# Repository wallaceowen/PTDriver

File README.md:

# PTDriver
Signal conditioning PT100 sensors for use with standard thermistor inputs on 3D printer control boards

## The schematic

## The board (KiCAD rendering)

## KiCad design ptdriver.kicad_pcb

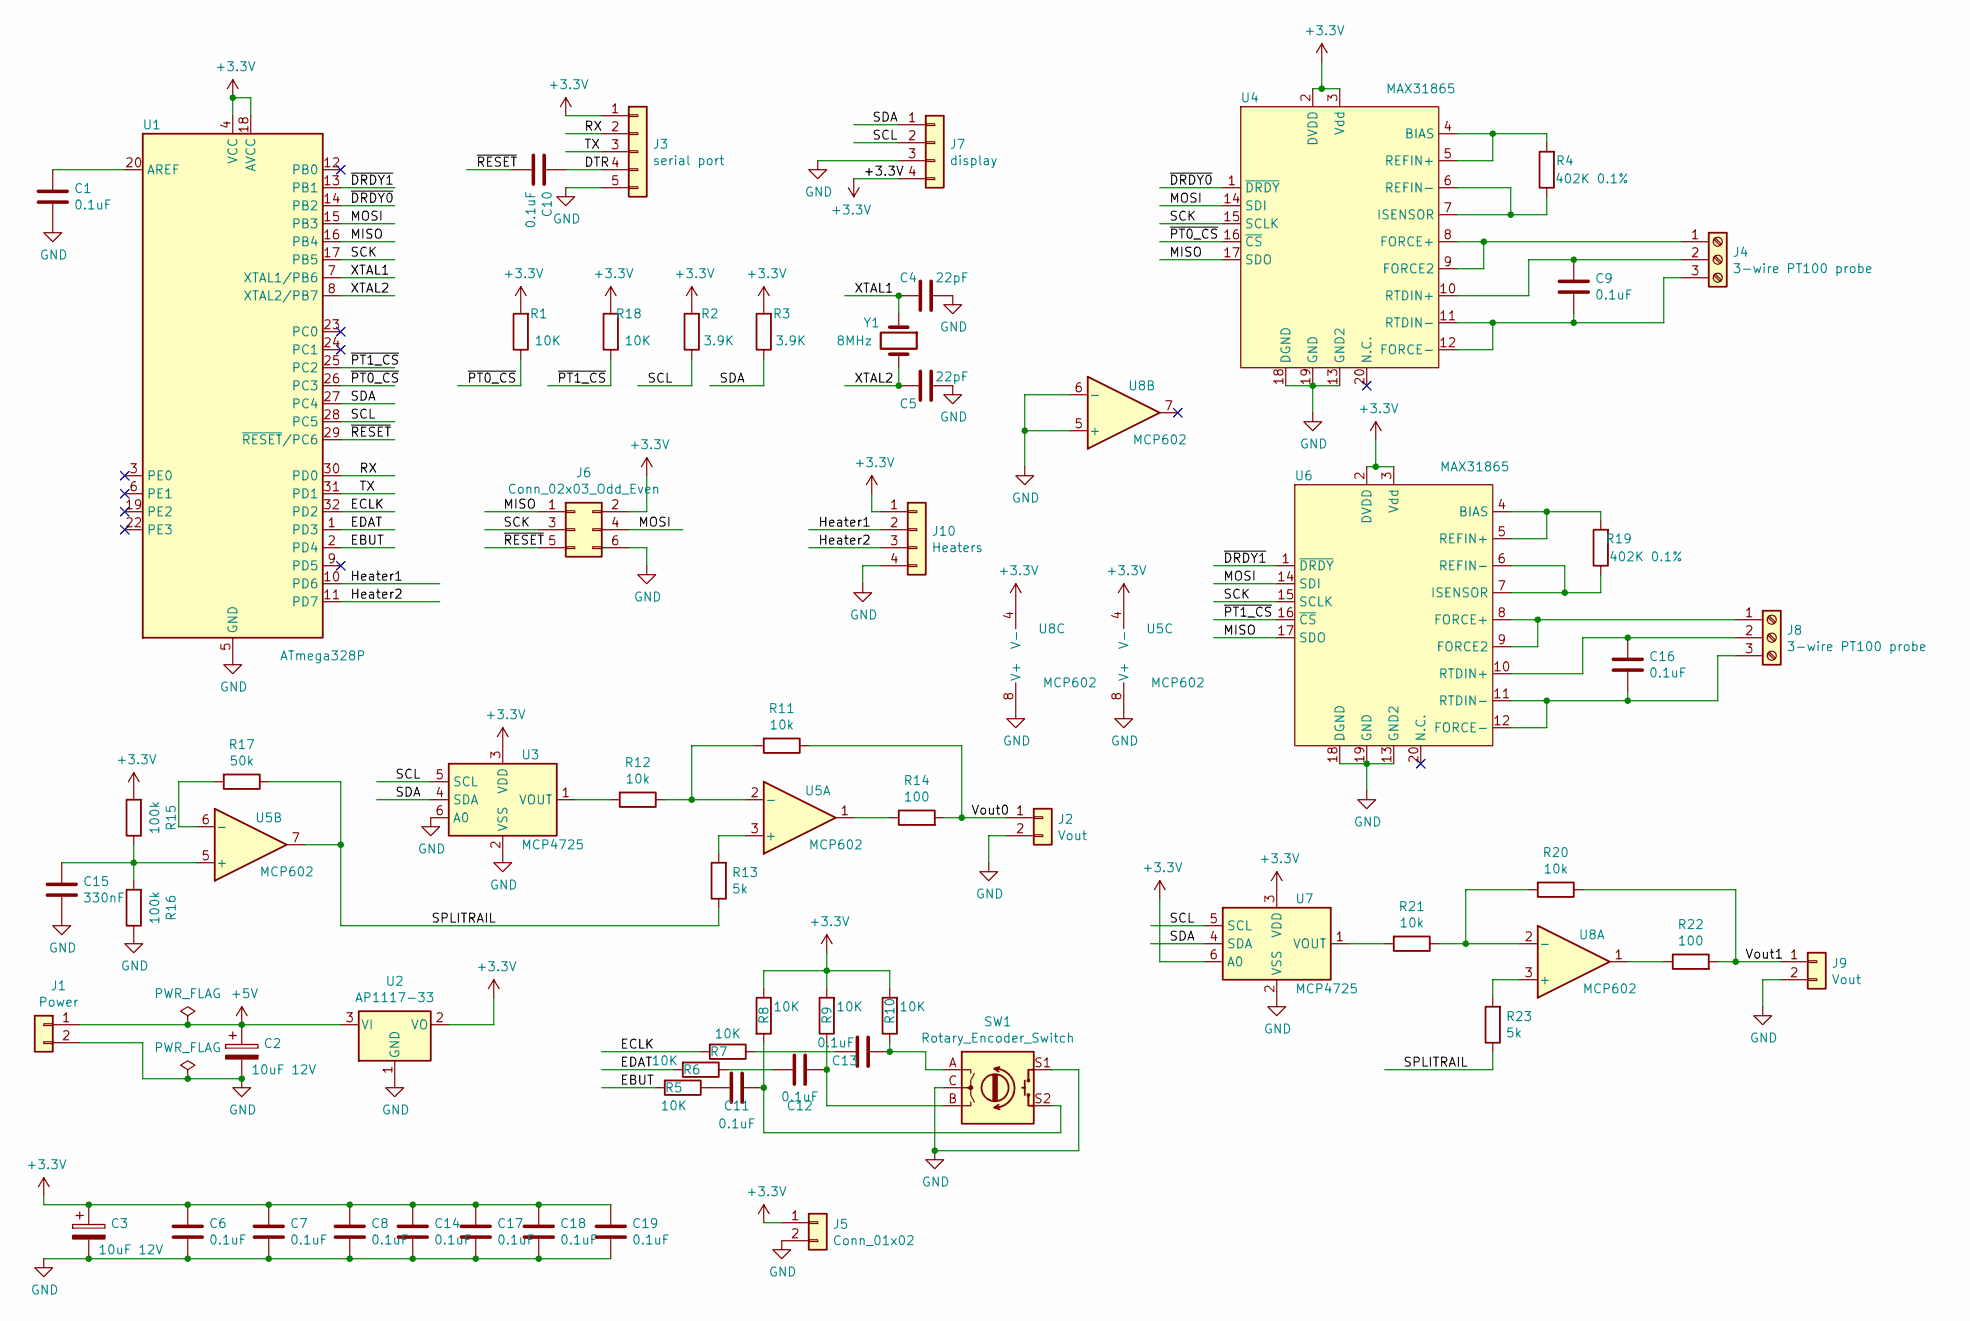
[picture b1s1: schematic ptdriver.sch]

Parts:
C1, C6, C7, C8, C9, C10, C14, C16, C17, C18, C19: 0.1uF; C_0805_2012Metric
C2, C3: 10uF 12V; C_2220_5650Metric
C4, C5: 22pF; C_0805_2012Metric
C11, C12, C13: 0.1uF; C_0603_1608Metric
C15: 330nF; C_0805_2012Metric
J1: Power; PinHeader_1x02_P2.54mm_Vertical
J2, J9: Vout; PinHeader_1x02_P2.54mm_Vertical
J3: serial port; PinHeader_1x05_P2.54mm_Vertical
J4, J8: 3-wire PT100 probe; TerminalBlock_4Ucon_1x03_P3.50mm_Vertical
J5: Conn_01x02; PinHeader_1x02_P2.54mm_Vertical
J6: Conn_02x03_Odd_Even; PinHeader_2x03_P2.54mm_Vertical
J7: display; PinHeader_1x04_P2.54mm_Vertical
J10: Heaters; PinHeader_1x04_P2.54mm_Vertical
R1, R5, R6, R7, R8, R9, R10, R18: 10K; R_0603_1608Metric
R2, R3: 3.9K; R_0603_1608Metric
R4, R19: 402K 0.1%; R_0805_2012Metric
R11, R12, R20, R21: 10k; R_0603_1608Metric
R13, R23: 5k; R_0603_1608Metric
R14, R22: 100; R_0603_1608Metric
R15, R16: 100k; R_0603_1608Metric
R17: 50k; R_0603_1608Metric
SW1: Rotary_Encoder_Switch; RotaryEncoder_Alps_EC12E-Switch_Vertical_H20mm_CircularMoun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
U1: ATmega328P; TQFP-32_7x7mm_P0.8mm
U2: AP1117-33; SOT-223-3_TabPin2
U3, U7: MCP4725; SOT-23-6_Handsoldering
U4, U6: MAX31865; SOP20_max
U5, U8: MCP602; SOIC-8_3.9x4.9mm_P1.27mm
Y1: 8MHz; Crystal_HC18-U_Vertical

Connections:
+3V3: C3.1, C6.1, C7.1, C8.1, C14.1, C17.1, C18.1, C19.1, J3.1, J5.1, J6.2, J7.4, J10.1, R1.2, R2.2, R3.2, R8.1, R9.2, R10.2, R15.2, R18.2, U1.4 (VCC), U1.18 (AVCC), U2.2 (VO), U3.3 (VDD), U4.2 (DVDD), U4.3 (Vdd), U5.4 (V-), U6.2 (DVDD), U6.3 (Vdd), U7.3 (VDD), U7.6 (A0), U8.4 (V-)
+5V: C2.1, J1.1, U2.3 (VI)
/DTR: C10.1, J3.4
/EBUT: R5.2, U1.2 (PD4)
/ECLK: R7.2, U1.32 (PD2)
/EDAT: R6.2, U1.1 (PD3)
/Heater1: J10.2, U1.10 (PD6)
/Heater2: J10.3, U1.11 (PD7)
/MISO: J6.1, U1.16 (PB4), U4.17 (SDO), U6.17 (SDO)
/MOSI: J6.4, U1.15 (PB3), U4.14 (SDI), U6.14 (SDI)
/RX: J3.2, U1.30 (PD0)
/SCK: J6.3, U1.17 (PB5), U4.15 (SCLK), U6.15 (SCLK)
/SCL: J7.2, R2.1, U1.28 (PC5), U3.5 (SCL), U7.5 (SCL)
/SDA: J7.1, R3.1, U1.27 (PC4), U3.4 (SDA), U7.4 (SDA)
/SPLITRAIL: R13.1, R17.1, R23.1, U5.7
/TX: J3.3, U1.31 (PD1)
/Vout0: J2.1, R11.1, R14.2
/Vout1: J9.1, R20.1, R22.2
/XTAL1: C4.2, U1.7 (XTAL1/PB6), Y1.1
/XTAL2: C5.2, U1.8 (XTAL2/PB7), Y1.2
/~DRDY0~: U1.14 (PB2), U4.1 (~DRDY~)
/~DRDY1~: U1.13 (PB1), U6.1 (~DRDY~)
/~PT0_CS~: R1.1, U1.26 (PC3), U4.16 (~CS~)
/~PT1_CS~: R18.1, U1.25 (PC2), U6.16 (~CS~)
/~RESET~: C10.2, J6.5, U1.29 (~RESET~/PC6)
GND: C1.2, C2.2, C3.2, C4.1, C5.1, C6.2, C7.2, C8.2, C14.2, C15.2, C17.2, C18.2, C19.2, J1.2, J2.2, J3.5, J5.2, J6.6, J7.3, J9.2, J10.4, R16.1, SW1.C, SW1.S1, U1.5 (GND), U1.21 (GND), U2.1 (GND), U3.2 (VSS), U3.6 (A0), U4.13 (GND2), U4.18 (DGND), U4.19 (GND), U5.8 (V+), U6.13 (GND2), U6.18 (DGND), U6.19 (GND), U7.2 (VSS), U8.5 (+), U8.6 (-), U8.8 (V+)
unnamed: C1.1, U1.20 (AREF)
unnamed: C9.1, J4.2, U4.10 (RTDIN+)
unnamed: C9.2, J4.3, U4.11 (RTDIN-), U4.12 (FORCE-)
unnamed: C11.1, R8.2, SW1.S2
unnamed: C11.2, R5.1
unnamed: C12.1, R9.1, SW1.B
unnamed: C12.2, R6.1
unnamed: C13.1, R10.1, SW1.A
unnamed: C13.2, R7.1
unnamed: C15.1, R15.1, R16.2, U5.5 (+)
unnamed: C16.1, J8.2, U6.10 (RTDIN+)
unnamed: C16.2, J8.3, U6.11 (RTDIN-), U6.12 (FORCE-)
unnamed: J4.1, U4.8 (FORCE+), U4.9 (FORCE2)
unnamed: J8.1, U6.8 (FORCE+), U6.9 (FORCE2)
unnamed: R4.1, U4.6 (REFIN-), U4.7 (ISENSOR)
unnamed: R4.2, U4.4 (BIAS), U4.5 (REFIN+)
unnamed: R11.2, R12.1, U5.2 (-)
unnamed: R12.2, U3.1 (VOUT)
unnamed: R13.2, U5.3 (+)
unnamed: R14.1, U5.1
unnamed: R17.2, U5.6 (-)
unnamed: R19.1, U6.6 (REFIN-), U6.7 (ISENSOR)
unnamed: R19.2, U6.4 (BIAS), U6.5 (REFIN+)
unnamed: R20.2, R21.1, U8.2 (-)
unnamed: R21.2, U7.1 (VOUT)
unnamed: R22.1, U8.1
unnamed: R23.2, U8.3 (+)

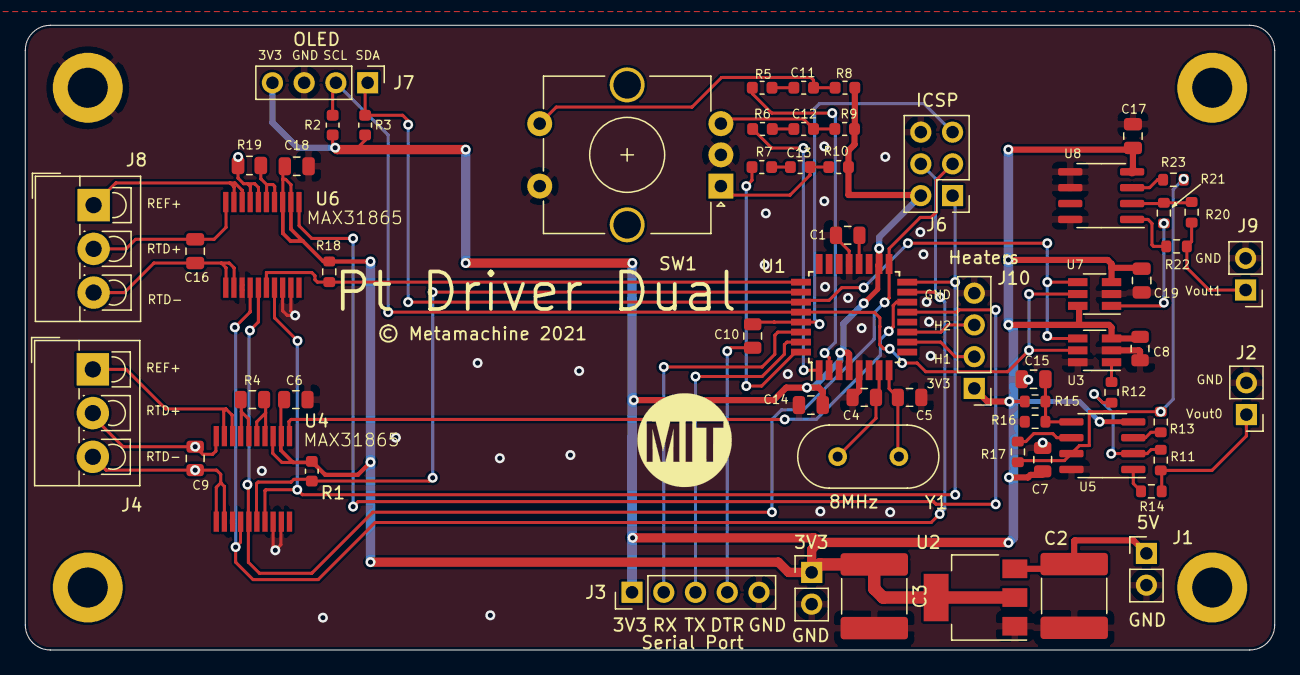
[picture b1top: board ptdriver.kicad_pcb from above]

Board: 2 copper layers, 100.0 x 50.0 mm, 64 parts (0 on the bottom side), 53 nets.

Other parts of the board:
M3, M3#2: MountingHole_3.2mm_M3_DIN965_Pad

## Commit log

2021-09-20 Add actual design into repo
2021-09-20 Add image of board to README
2021-09-20 Re-arrange and rename things to survive a move from one folder to another
2021-09-21 Add schematic pdf
2021-09-21 Add .gitignore
2021-09-24 Update picture of board; Fix a couple of windy traces
2021-09-24 Point to new png of schematic instead of pdf; toss pdf
2021-09-24 Add the schematic png

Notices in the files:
ptdriver.kicad_pcb:
© Metamachine 2021
